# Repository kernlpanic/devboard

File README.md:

# Devboard 

## Description

Just a small devboard with ethernet and rs232 interface.
Almost(tm) fully THD Design with two exceptions. One is the ethernet controller and the other one is the sram module.
The main microcontroller is an Atmega32.
The full BOM I used to build this board will soon be added here

## Disclaimer

This pcb design is still work in progress and not fully testet. 
Still feel free to use it and to contact me if you like to give some advice for improvement

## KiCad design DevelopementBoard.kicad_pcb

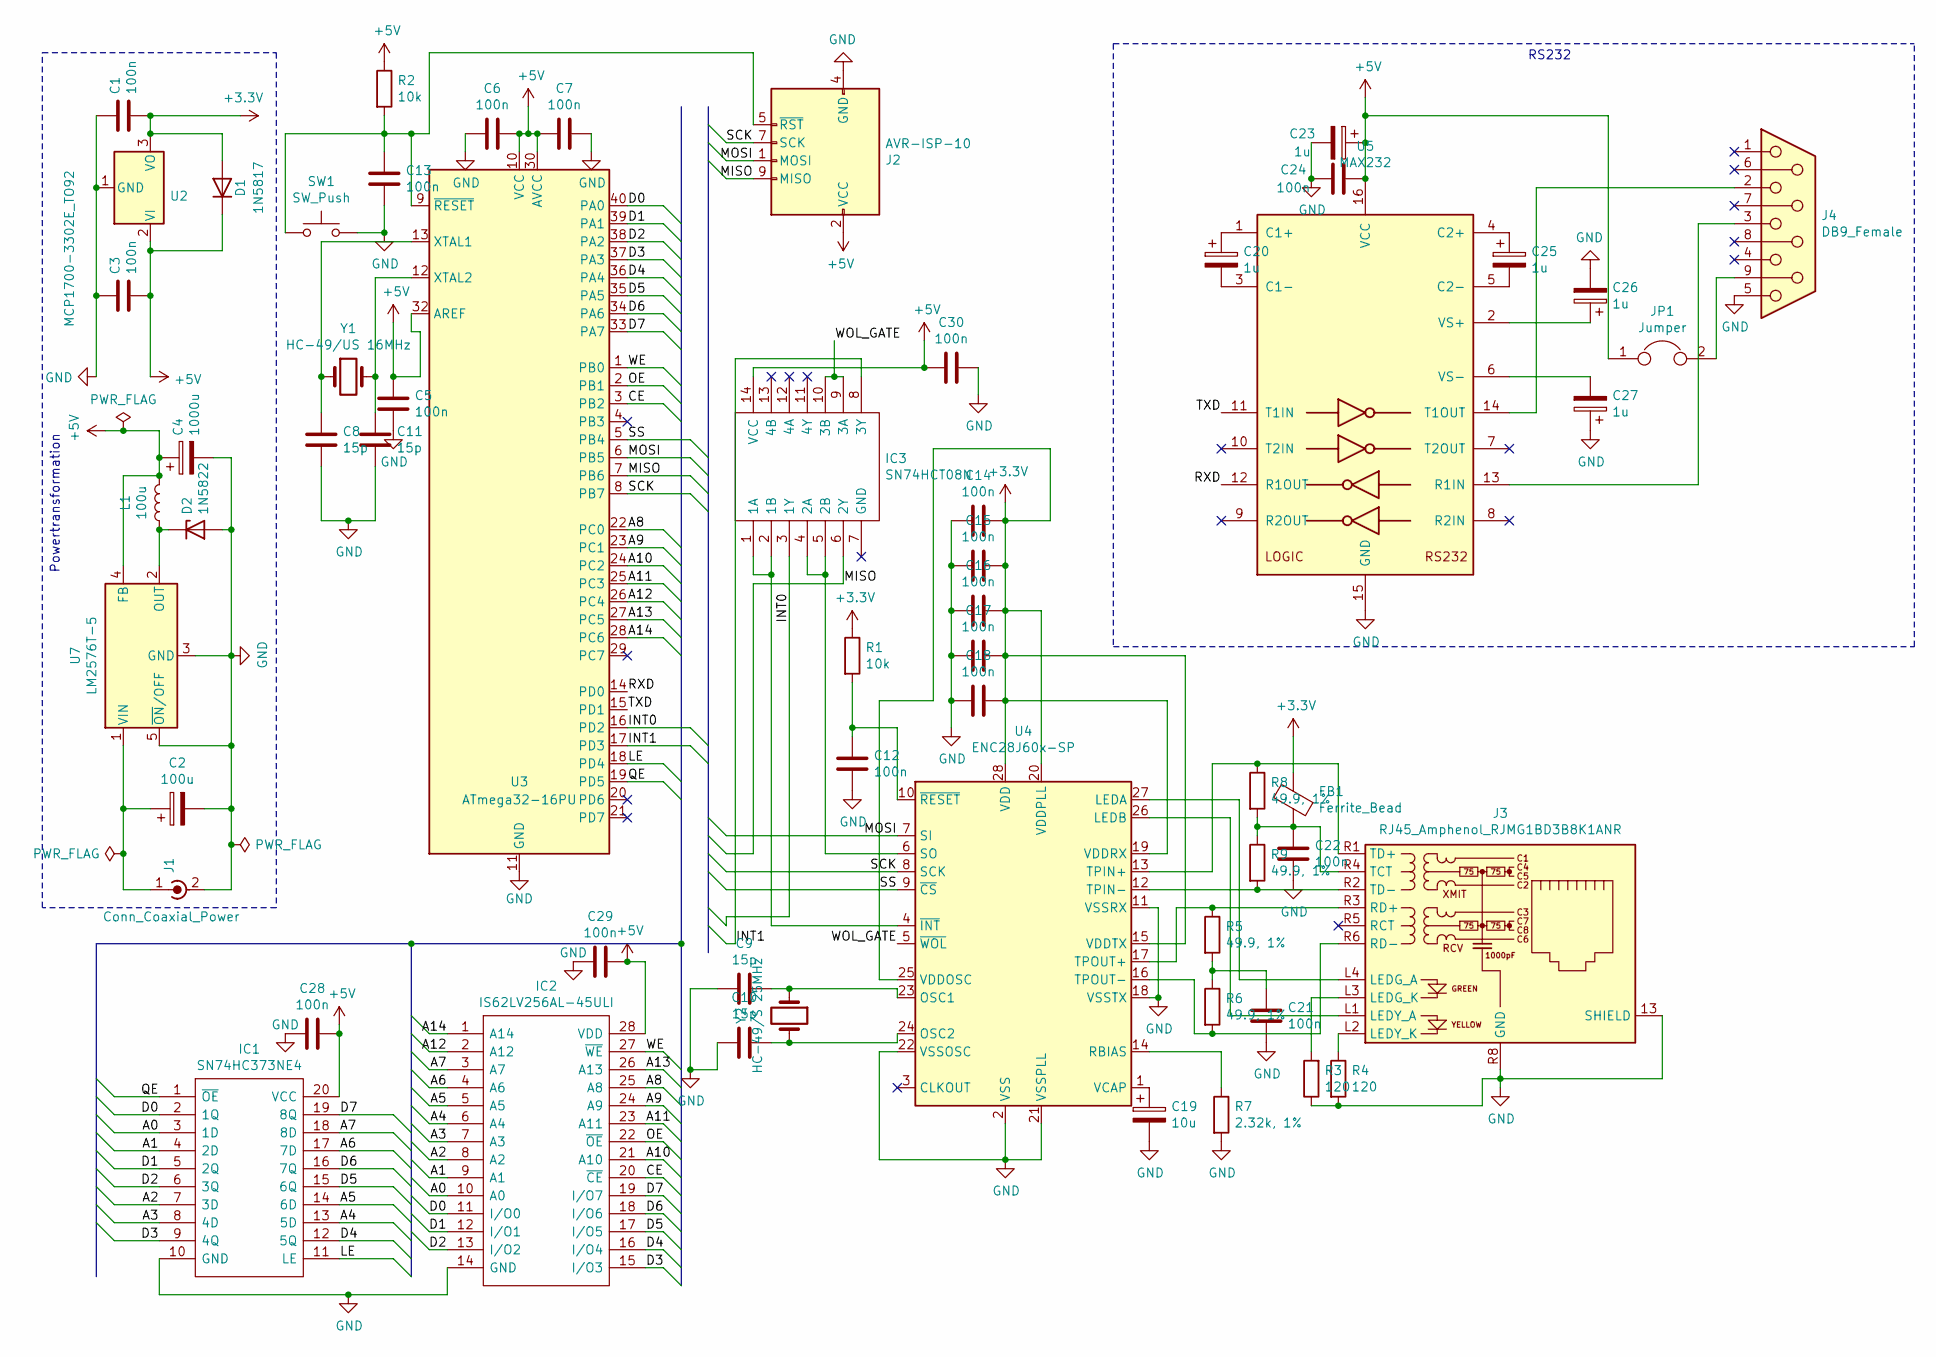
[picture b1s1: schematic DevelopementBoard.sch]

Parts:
C1, C3, C5, C6, C7, C12, C13, C14, C15, C16, C17, C18, C21, C22, C24, C28, C29, C30: 100n; C_Disc_D5.0mm_W2.5mm_P5.00mm
C2: 100u; CP_Radial_D8.0mm_P3.50mm
C4: 1000u; CP_Radial_D10.0mm_P5.00mm
C8, C9, C10, C11: 15p; C_Disc_D5.0mm_W2.5mm_P5.00mm
C19: 10u; CP_Radial_D5.0mm_P2.50mm
C20, C23, C25, C26, C27: 1u; CP_Radial_D5.0mm_P2.50mm
D1: 1N5817; D_DO-41_SOD81_P7.62mm_Horizontal
D2: 1N5822; D_DO-201AD_P12.70mm_Horizontal
FB1: Ferrite_Bead; INDAD2070W65L670D350
IC1: SN74HC373NE4; DIP794W53P254L2540H508Q20N; Mouser Part Number 595-SN74HC373NE4
IC2: IS62LV256AL-45ULI; SOIC127P1210X305-28N; Mouser Part Number 870-IS62LV256AL45ULI
IC3: SN74HCT08N; DIP794W53P254L1930H508Q14N; Mouser Part Number 595-SN74HCT08N
J1: Conn_Coaxial_Power; PJ037A
J2: AVR-ISP-10; PinHeader_2x05_P2.54mm_Vertical
J3: RJ45_Amphenol_RJMG1BD3B8K1ANR
J4: DB9_Female; DSUB-9_Female_Horizontal_P2.77x2.84mm_EdgePinOffset7.70mm_H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
JP1: Jumper; PinHeader_1x02_P2.54mm_Vertical
L1: 100u; L_Axial_L7.0mm_D3.3mm_P10.16mm_Horizontal_Fastron_MICC
R1, R2: 10k; R_Axial_DIN0207_L6.3mm_D2.5mm_P10.16mm_Horizontal
R3, R4: 120; R_Axial_DIN0207_L6.3mm_D2.5mm_P15.24mm_Horizontal
R5, R6, R8, R9: 49.9, 1%; R_Axial_DIN0207_L6.3mm_D2.5mm_P10.16mm_Horizontal
R7: 2.32k, 1%; R_Axial_DIN0204_L3.6mm_D1.6mm_P7.62mm_Horizontal
SW1: SW_Push; SW_PUSH_6mm
U2: MCP1700-3302E_TO92; TO-92_Inline_Wide
U3: ATmega32-16PU; DIP-40_W15.24mm_LongPads
U4: ENC28J60x-SP; SOIC-28W_7.5x17.9mm_P1.27mm
U5: MAX232; DIP-16_W7.62mm_LongPads
U7: LM2576T-5; TO-220-5_Vertical
Y1: HC-49/US 16MHz; Crystal_HC49-U_Vertical
Y2: HC-49/S 25MHz; Crystal_HC49-U_Vertical

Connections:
+3V3: C1.2, C14.1, C15.1, C16.1, C17.1, C18.1, D1.2 (A), FB1.2, R1.1, U2.3 (VO), U4.15 (VDDTX), U4.19 (VDDRX), U4.20 (VDDPLL), U4.25 (VDDOSC), U4.28 (VDD)
+5V: C3.2, C4.1, C5.1, C6.1, C7.2, C23.1, C24.1, C28.1, C29.1, C30.2, D1.1 (K), IC1.20 (VCC), IC2.28 (VDD), IC3.14 (VCC), J2.2 (VCC), JP1.1, L1.2, R2.1, U2.2 (VI), U3.10 (VCC), U3.30 (AVCC), U3.32 (AREF), U5.16 (VCC), U7.4 (FB)
/A0: IC1.3 (1D), IC2.10 (A0)
/A1: IC1.4 (2D), IC2.9 (A1)
/A2: IC1.7 (3D), IC2.8 (A2)
/A3: IC1.8 (4D), IC2.7 (A3)
/A4: IC1.13 (5D), IC2.6 (A4)
/A5: IC1.14 (6D), IC2.5 (A5)
/A6: IC1.17 (7D), IC2.4 (A6)
/A7: IC1.18 (8D), IC2.3 (A7)
/A8: IC2.25 (A8), U3.22 (PC0)
/A9: IC2.24 (A9), U3.23 (PC1)
/A10: IC2.21 (A10), U3.24 (PC2)
/A11: IC2.23 (A11), U3.25 (PC3)
/A12: IC2.2 (A12), U3.26 (PC4)
/A13: IC2.26 (A13), U3.27 (PC5)
/A14: IC2.1 (A14), U3.28 (PC6)
/CE: IC2.20 (~CE), U3.3 (PB2)
/D0: IC1.2 (1Q), IC2.11 (I/O0), U3.40 (PA0)
/D1: IC1.5 (2Q), IC2.12 (I/O1), U3.39 (PA1)
/D2: IC1.6 (3Q), IC2.13 (I/O2), U3.38 (PA2)
/D3: IC1.9 (4Q), IC2.15 (I/O3), U3.37 (PA3)
/D4: IC1.12 (5Q), IC2.16 (I/O4), U3.36 (PA4)
/D5: IC1.15 (6Q), IC2.17 (I/O5), U3.35 (PA5)
/D6: IC1.16 (7Q), IC2.18 (I/O6), U3.34 (PA6)
/D7: IC1.19 (8Q), IC2.19 (I/O7), U3.33 (PA7)
/INT0: IC3.3 (1Y), U3.16 (PD2)
/INT1: IC3.8 (3Y), U3.17 (PD3)
/LE: IC1.11 (LE), U3.18 (PD4)
/MISO: IC3.6 (2Y), J2.9 (MISO), U3.7 (PB6)
/MOSI: J2.1 (MOSI), U3.6 (PB5), U4.7 (SI)
/OE: IC2.22 (~OE), U3.2 (PB1)
/QE: IC1.1 (~OE), U3.19 (PD5)
/RXD: U3.14 (PD0), U5.12 (R1OUT)
/SCK: J2.7 (SCK), U3.8 (PB7), U4.8 (SCK)
/SS: U3.5 (PB4), U4.9 (~CS)
/TXD: U3.15 (PD1), U5.11 (T1IN)
/WE: IC2.27 (~WE), U3.1 (PB0)
/WOL_GATE: IC3.9 (3A), IC3.10 (3B), U4.5 (~WOL)
GND: C1.1, C2.2, C3.1, C4.2, C5.2, C6.2, C7.1, C8.2, C9.2, C10.2, C11.2, C12.2, C13.2, C14.2, C15.2, C16.2, C17.2, C18.2, C19.2, C21.2, C22.2, C23.2, C24.2, C26.2, C27.1, C28.2, C29.2, C30.1, D2.2 (A), IC1.10 (GND), IC2.14 (GND), J1.2 (Ext), J2.4 (GND), J2.6 (GND), J2.8 (GND), J2.10 (GND), J3.13 (SHIELD), J3.R8 (GND), J4.5, R3.1, R4.2, R7.2, SW1.2, U2.1 (GND), U3.11 (GND), U3.31 (GND), U4.2 (VSS), U4.11 (VSSRX), U4.18 (VSSTX), U4.21 (VSSPLL), U4.22 (VSSOSC), U5.15 (GND), U7.3 (GND), U7.5 (~ON~/OFF)
unnamed: C2.1, J1.1 (In), U7.1 (VIN)
unnamed: C8.1, U3.13 (XTAL1), Y1.1
unnamed: C9.1, U4.23 (OSC1), Y2.1
unnamed: C10.1, U4.24 (OSC2), Y2.2
unnamed: C11.1, U3.12 (XTAL2), Y1.2
unnamed: C12.1, R1.2, U4.10 (~RESET)
unnamed: C13.1, J2.5 (~RST), R2.2, SW1.1, U3.9 (~RESET)
unnamed: C19.1, U4.1 (VCAP)
unnamed: C20.1, U5.1 (C1+)
unnamed: C20.2, U5.3 (C1-)
unnamed: C21.1, R5.2, R6.1
unnamed: C22.1, FB1.1, J3.R4 (TCT), R8.2, R9.1
unnamed: C25.1, U5.4 (C2+)
unnamed: C25.2, U5.5 (C2-)
unnamed: C26.1, U5.2 (VS+)
unnamed: C27.2, U5.6 (VS-)
unnamed: D2.1 (K), L1.1, U7.2 (OUT)
unnamed: IC3.1 (1A), IC3.2 (1B), U4.4 (~INT)
unnamed: IC3.4 (2A), IC3.5 (2B), U4.6 (SO)
unnamed: J3.L1 (LEDY_A), U4.26 (LEDB)
unnamed: J3.L2 (LEDY_K), R4.1
unnamed: J3.L3 (LEDG_K), R3.2
unnamed: J3.L4 (LEDG_A), U4.27 (LEDA)
unnamed: J3.R1 (TD+), R8.1, U4.13 (TPIN+)
unnamed: J3.R2 (TD-), R9.2, U4.12 (TPIN-)
unnamed: J3.R3 (RD+), R5.1, U4.17 (TPOUT+)
unnamed: J3.R6 (RD-), R6.2, U4.16 (TPOUT-)
unnamed: J4.2, U5.14 (T1OUT)
unnamed: J4.3, U5.13 (R1IN)
unnamed: J4.9, JP1.2
unnamed: R7.1, U4.14 (RBIAS)

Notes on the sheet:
RS232
Powertransformation

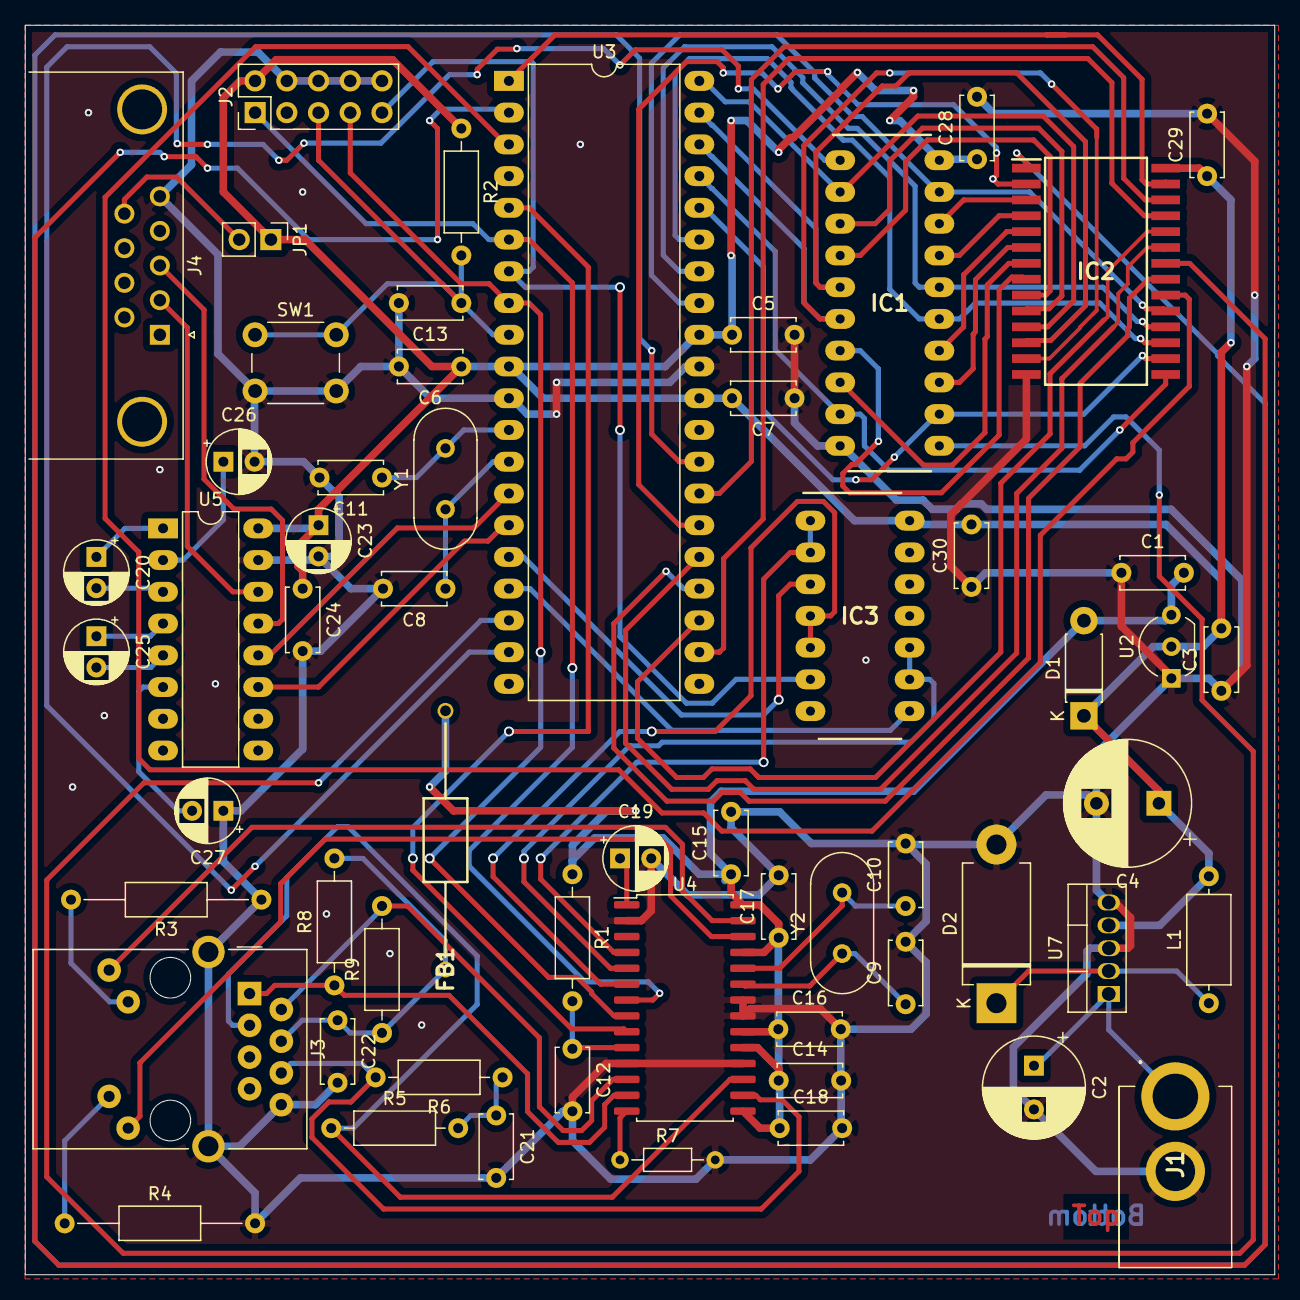
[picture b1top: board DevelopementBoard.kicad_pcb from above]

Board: 2 copper layers, 100.0 x 100.0 mm, 59 parts (0 on the bottom side), 71 nets.

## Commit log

2020-10-30 init commit
2020-10-30 update board
2020-11-09 add ethernet to board
2020-11-10 rearrange symbols
2020-11-10 add part libraries
2020-11-11 add and gate libraries
2020-11-12 finish first version of board
2020-11-14 update libraries
2020-11-14 add most footprints to schematics
2020-11-15 add missing footprints
2020-11-15 add another sram libraries
2020-11-15 place initial layout
2020-11-16 fix pad clearance problems
2020-11-17 connect most parts
2020-11-17 draw all connections
2020-11-17 fix layout and draw gnd planes
2020-11-17 finish pcb design
2020-11-17 add title to board
2020-11-17 add some vias for the gnd plane
2020-11-17 add 3D objects to footprints
2022-03-01 rename project
